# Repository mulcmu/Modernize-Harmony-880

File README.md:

# Modernize Harmony 880
 Modernize a Logitech Harmony 880 universal remote

# Details

The Logitech Harmony 880 is a universal infrared remote intended to control the numerous parts of a home theater system with one remote. The Harmony remotes are programmable allowing sequences of IR commands to be sent to start an activity. So "Watch Blu-ray" could be configured to turn on TV, receiver, and blu-ray player player, and set TV and receiver to correct inputs. Convenient to keep from needing numerous remotes to start an activity. Programming is performed using Logitech internet based software to update the remote via a USB connection. In 2021, Logitech announced that they would discontinue Harmony Remote [manufacturing](https://support.logi.com/hc/en-us/community/posts/1500000658341). The release indicates support would still continue software support, who knows how long that will remain.

The 880 remote build is great quality. I'm not sure exactly when I got mine but it is upwards of 15 years of service with only some cosmetic wear to the buttons. It has a rechargeable battery, that charges in a storage cradle. Over the years the universality of the remote has diminished as more devices use RF remote protocols. To keep the 880 working after getting a Roku box, an ESP8266 needed to be setup to [translate IR remote](https://github.com/mulcmu/IRtoRokuBridge) signals to HTTP POST commands.

This project is undertaking an upgrade for the 880 universal remote to, update screen to TFT with better resolution, build in wifi connectivity, and provide an open source software solution for setup and programming.

Current PCB design has all existing remote features implemented, hardware and software testing in process.

# Project Logs

https://hackaday.io/project/185926-modernize-harmony-880

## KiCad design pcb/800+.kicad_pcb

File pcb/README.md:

# Alpha3 PCB

Alpha3 PCB designed and ordered to test the peripheral operation.  Should be functionally complete if everything works.

There are some clearance issues with the bottom of remote case screw bosses interfering with parts on bottom of board.

# Alpha2 PCB

Updated the Kicad project for another alpha PCB.  Two layer PCB again but 0.8mm thick to fully test fitup with case.

* Fixed mosfet for the button led backlight
* Put an ESP32-S3 module on the board.
* USB wired up to the ESP32, 3.3V supply from the usb 5V.

# Alpha PCB

Kicad files for the alpha PCB.  Overall dimensions were okay.  The sides by the LCD might need trimmed down a smidge but there isn't much room for the button contacts.

Two layer PCB to keep cost down.  I ordered a 1.6mm thick but the stock board was 0.8mm so the case wouldn't snap shut properly.

##### Bare Screen

https://www.alibaba.com/product-detail/Lcd-Screen-Display-2-Inch-240x320_1600053711661.html

##### 4mm dome switches

https://www.aliexpress.us/item/2255799854582341

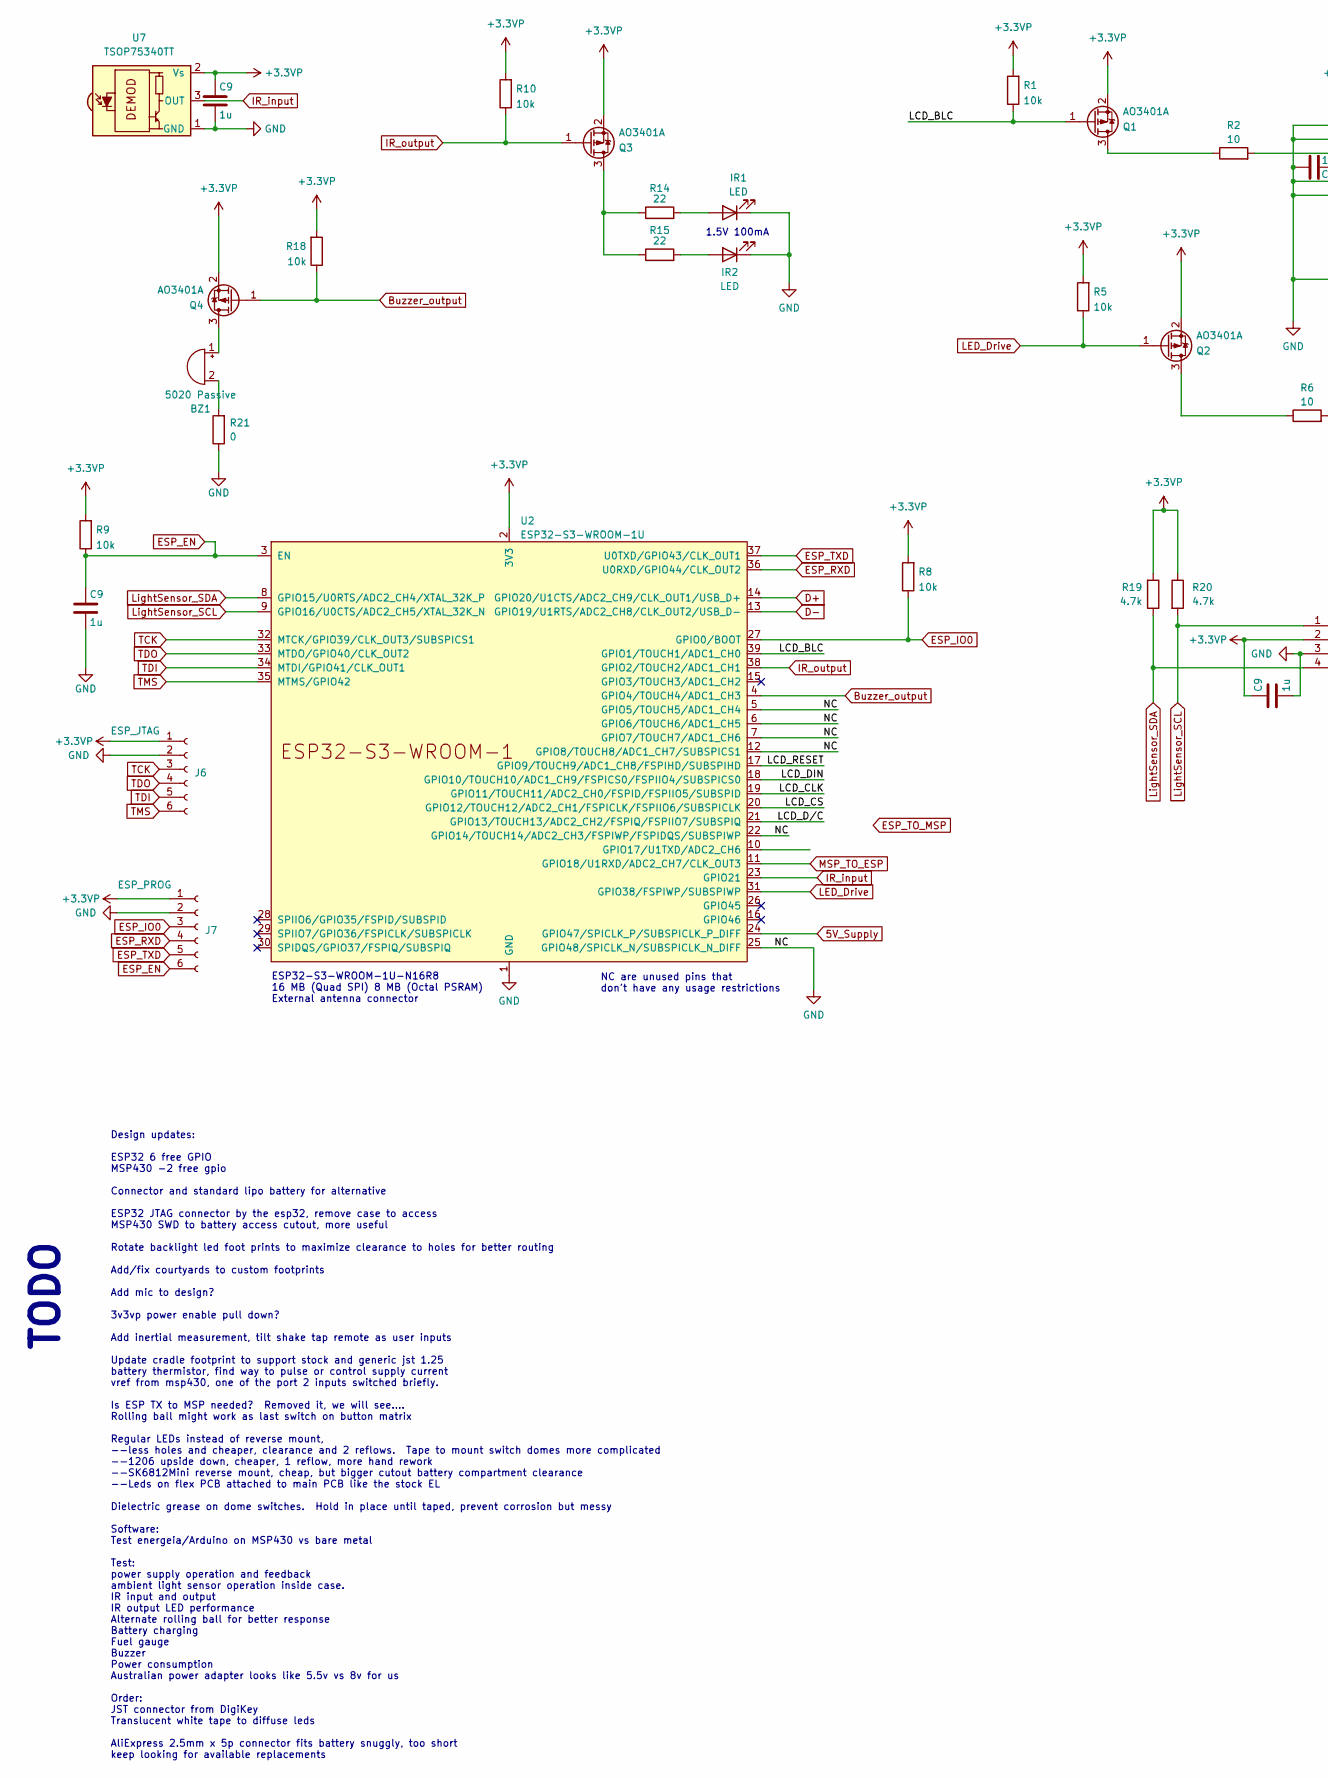
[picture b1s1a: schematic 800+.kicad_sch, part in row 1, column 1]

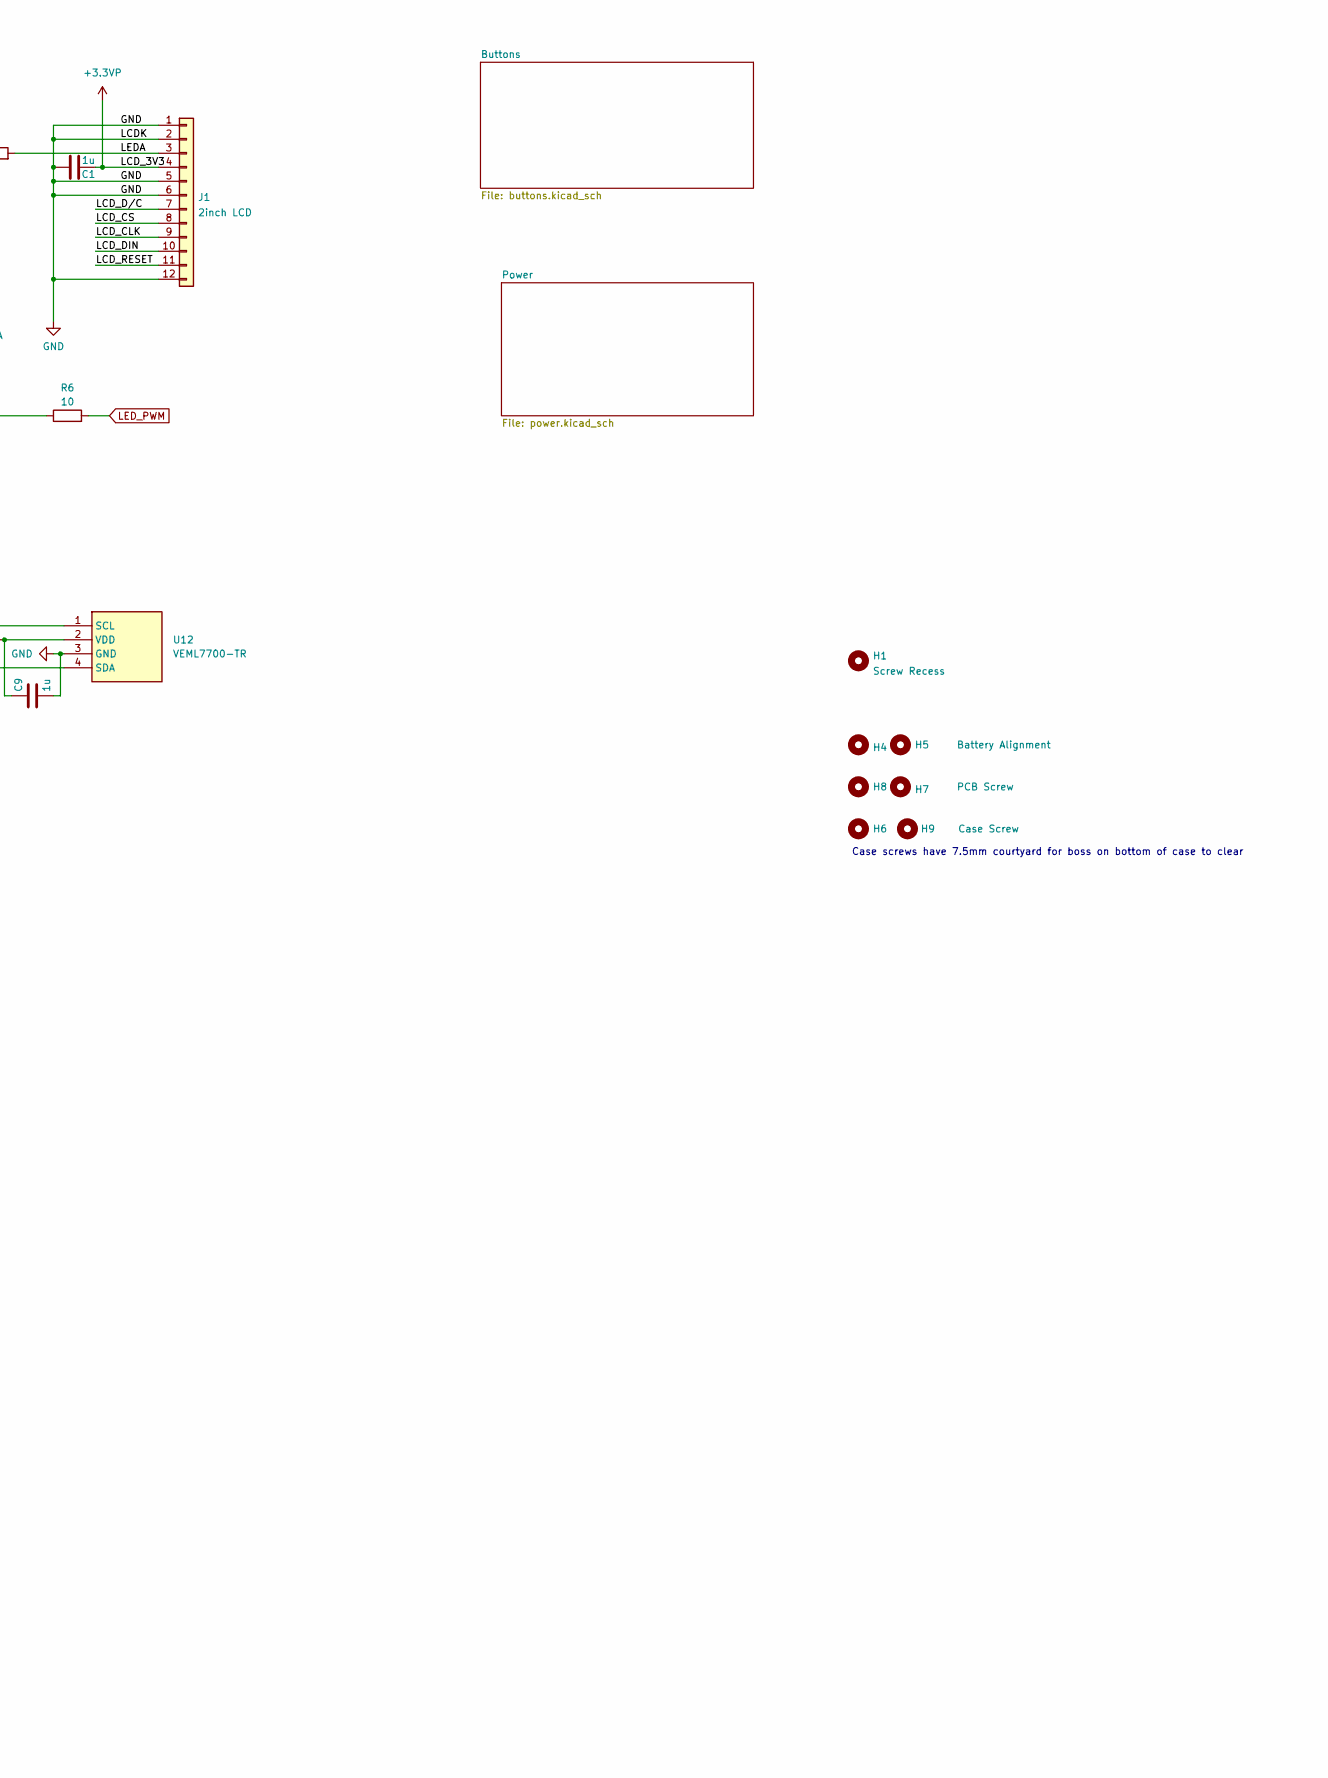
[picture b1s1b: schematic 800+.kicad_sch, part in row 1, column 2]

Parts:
BZ1: 5020 Passive; 5020passiveBuzzer
C1, C9: 1u; C_0805_2012Metric
H1: Screw Recess; MountingHole_5mm
H4, H5: Battery Alignment; MountingHole_2.1mm
H6, H9: Case Screw; MountingHole_Boss
H7, H8: PCB Screw; MountingHole_2.2mm_M2
IR1, IR2: LED; IR_led
J1: 2inch LCD; 2inch_LCD
J6: ESP_JTAG; PinHeader_1x06_P2.54mm_Vertical
J7: ESP_PROG; PinHeader_1x06_P2.54mm_Vertical
Q1, Q2, Q3, Q4: AO3401A; SOT-23
R1, R5, R8, R9, R10, R18: 10k; R_0805_2012Metric
R2, R6: 10; R_1210_3225Metric
R14, R15: 22; R_1210_3225Metric
R19, R20: 4.7k; R_0805_2012Metric
R21: 0; R_1206_3216Metric
U2: ESP32-S3-WROOM-1U; ESP32-S3-WROOM-1
U7: TSOP75340TT; IR_input
U12: VEML7700-TR; VEML7700; Mouser Part Number 78-VEML7700-TT

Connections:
5V_Supply: U2.24 (GPIO47/SPICLK_P/SUBSPICLK_P_DIFF); also elsewhere on the board
/LCD_BLC: Q1.1 (G), R1.1, U2.39 (GPIO1/TOUCH1/ADC1_CH0)
/LCD_CLK: J1.9, U2.19 (GPIO11/TOUCH11/ADC2_CH0/FSPID/FSPIIO5/S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)
/LCD_CS: J1.8, U2.20 (GPIO12/TOUCH12/ADC2_CH1/FSPICLK/FSPIIO6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)
/LCD_DIN: J1.10, U2.18 (GPIO10/TOUCH10/ADC1_CH9/FSPICS0/FSPIIO4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)
/LCD_D/C: J1.7, U2.21 (GPIO13/TOUCH13/ADC2_CH2/FSPIQ/FSPIIO7/S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)
/LCD_RESET: J1.11, U2.17 (GPIO9/TOUCH9/ADC1_CH8/FSPIHD/SUBSPIHD)
/LEDA: J1.3, R2.2
Buzzer_output: Q4.1 (G), R18.1, U2.4 (GPIO4/TOUCH4/ADC1_CH3)
D+: U2.14 (GPIO20/U1CTS/ADC2_CH9/CLK_OUT1/USB_D+); also elsewhere on the board
D-: U2.13 (GPIO19/U1RTS/ADC2_CH8/CLK_OUT2/USB_D-); also elsewhere on the board
ESP_IO0: J7.3, R8.1, U2.27 (GPIO0/BOOT)
ESP_RXD: J7.4, U2.36 (U0RXD/GPIO44/CLK_OUT2)
ESP_TXD: J7.5, U2.37 (U0TXD/GPIO43/CLK_OUT1)
GND: C1.1, C9.2, IR1.1 (K), IR2.1 (K), J1.1, J1.2, J1.5, J1.6, J1.12, J6.2, J7.2, R21.1, U2.1 (GND), U2.5 (GPIO5/TOUCH5/ADC1_CH4), U2.6 (GPIO6/TOUCH6/ADC1_CH5), U2.7 (GPIO7/TOUCH7/ADC1_CH6), U2.12 (GPIO8/TOUCH8/ADC1_CH7/SUBSPICS1), U2.22 (GPIO14/TOUCH14/ADC2_CH3/FSPIWP/FSPIDQS/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), U2.25 (GPIO48/SPICLK_N/SUBSPICLK_N_DIFF), U2.40 (GND), U2.41 (GND), U7.1 (GND), U12.3 (GND); also elsewhere on the board
IR_input: U2.23 (GPIO21), U7.3 (OUT)
IR_output: Q3.1 (G), R10.1, U2.38 (GPIO2/TOUCH2/ADC1_CH1)
LED_Drive: Q2.1 (G), R5.1, U2.31 (GPIO38/FSPIWP/SUBSPIWP)
LED_PWM: R6.2; also elsewhere on the board
LightSensor_SCL: R20.2, U2.9 (GPIO16/U0CTS/ADC2_CH5/XTAL_32K_N), U12.1 (SCL)
LightSensor_SDA: R19.1, U2.8 (GPIO15/U0RTS/ADC2_CH4/XTAL_32K_P), U12.4 (SDA)
MSP_TO_ESP: U2.11 (GPIO18/U1RXD/ADC2_CH7/CLK_OUT3); also elsewhere on the board
unnamed: BZ1.1 (+), Q4.3 (D)
unnamed: BZ1.2 (-), R21.2
unnamed: IR1.2 (A), R14.2
unnamed: IR2.2 (A), R15.2
unnamed: Q1.3 (D), R2.1
unnamed: Q2.3 (D), R6.1
unnamed: Q3.3 (D), R14.1, R15.1
TCK: J6.3, U2.32 (MTCK/GPIO39/CLK_OUT3/SUBSPICS1)
TDI: J6.5, U2.34 (MTDI/GPIO41/CLK_OUT1)
TDO: J6.4, U2.33 (MTDO/GPIO40/CLK_OUT2)
TMS: J6.6, U2.35 (MTMS/GPIO42)

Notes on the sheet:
NC are unused pins that don't have any usage restrictions
TODO
Case screws have 7.5mm courtyard for boss on bottom of case to clear
1.5V 100mA
Design updates: ESP32 6 free GPIO MSP430 -2 free gpio Connector and standard lipo battery for alternative ESP32 JTAG connector by the esp32, remove case to access MSP430 SWD to battery access cutout, more useful Rotate backlight led foot prints to maximize clearance to holes for better routing Add/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
ESP32-S3-WROOM-1U-N16R8 16 MB (Quad SPI) 8 MB (Octal PSRAM) External antenna connector

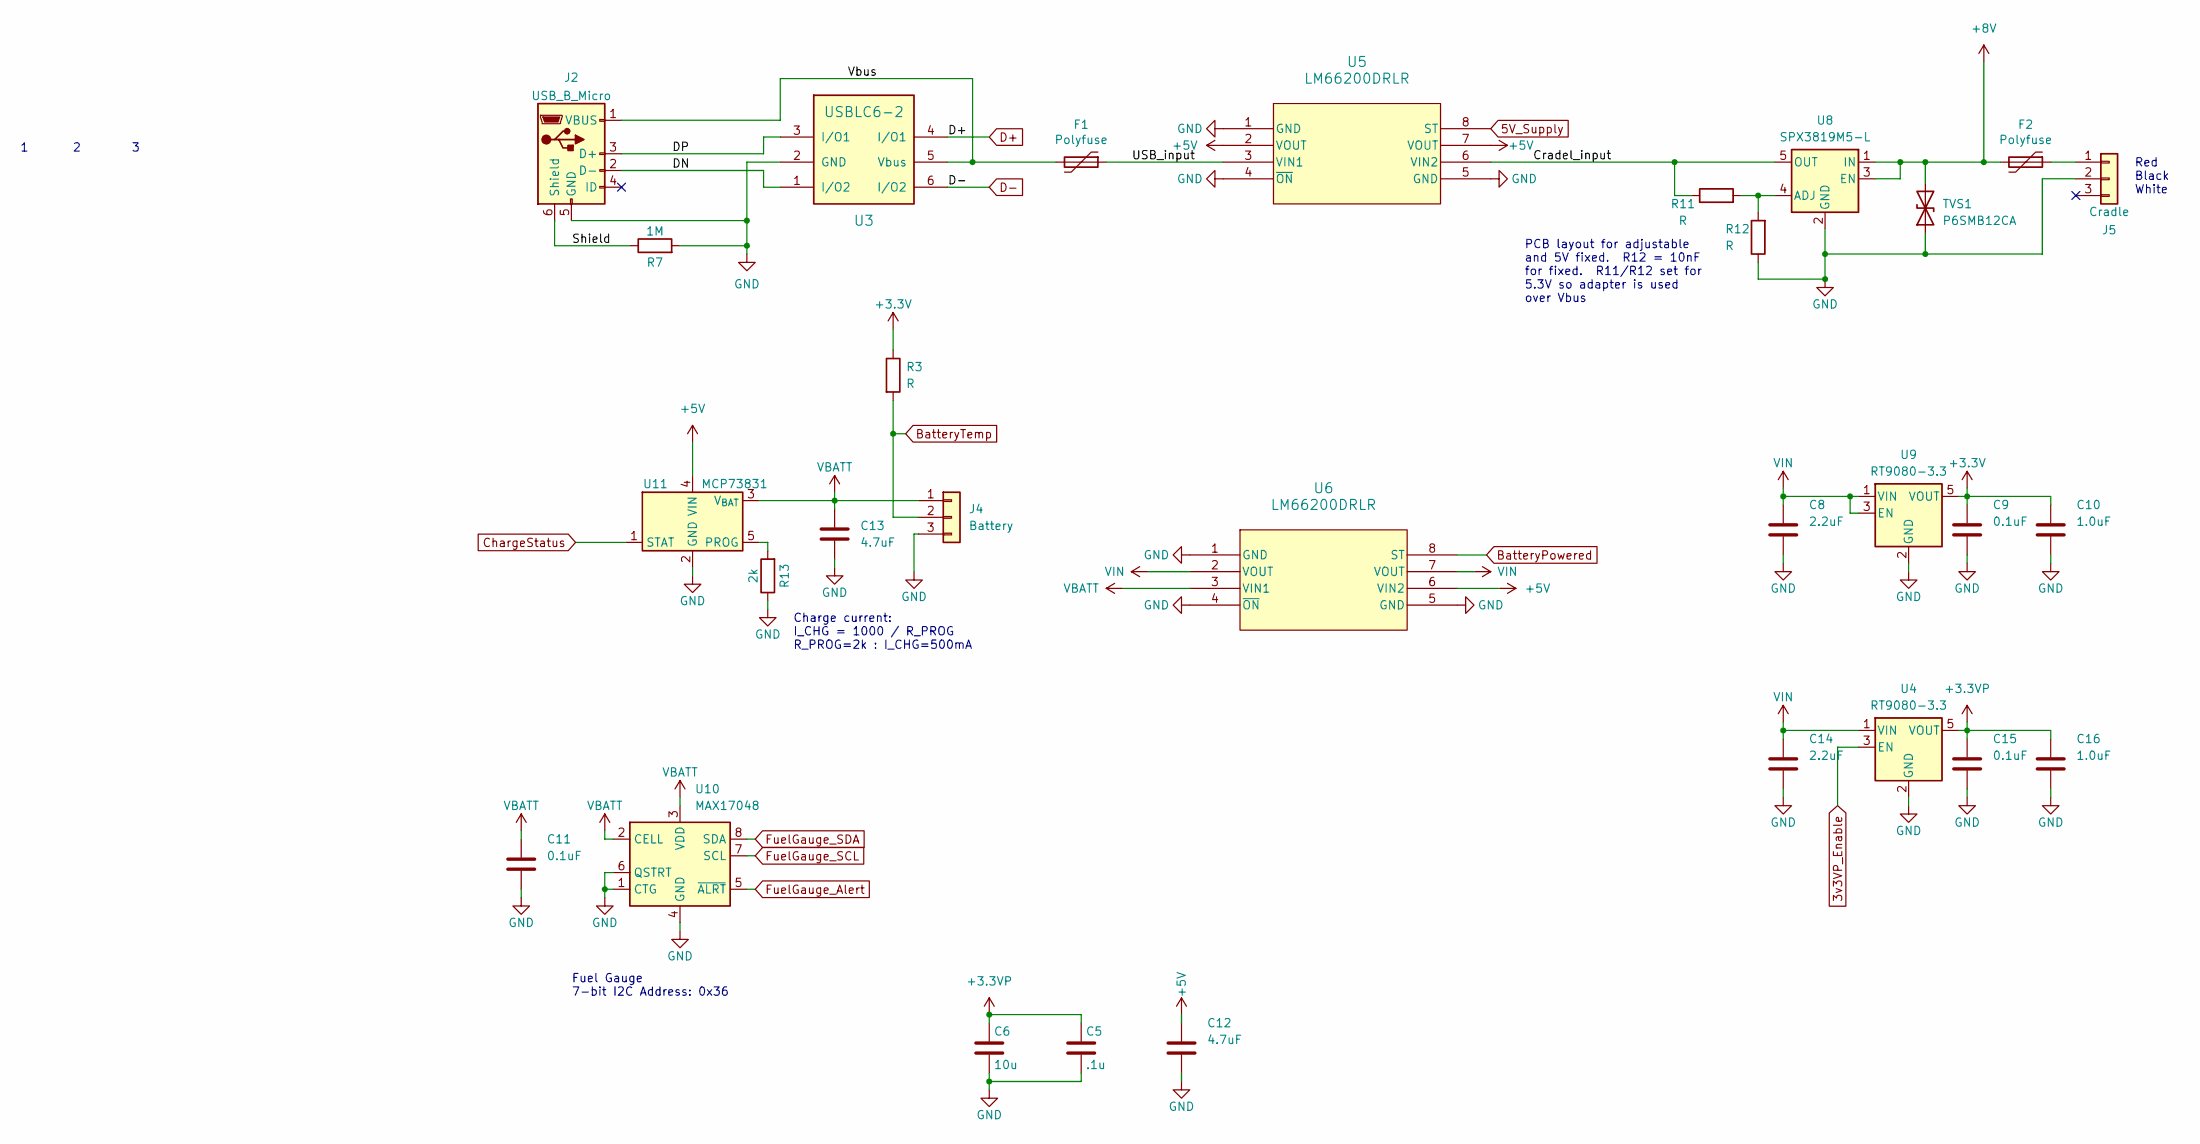
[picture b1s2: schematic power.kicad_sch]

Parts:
C5: .1u; C_0805_2012Metric
C6: 10u; C_0805_2012Metric
C8, C14: 2.2uF; C_0805_2012Metric
C9, C11, C15: 0.1uF; C_0805_2012Metric
C10, C16: 1.0uF; C_0805_2012Metric
C12, C13: 4.7uF; C_0805_2012Metric
F1, F2: Polyfuse; R_1210_3225Metric_Pad1.30x2.65mm_HandSolder
J2: USB_B_Micro; USB_Mini-B_Wuerth_65100516121_Horizontal
J4: Battery; Battery_reuse
J5: Cradle; JST_GH_BM03B-GHS-TBT_1x03-1MP_P1.25mm_Vertical
R3, R11, R12: R; R_0805_2012Metric
R7: 1M; R_0805_2012Metric
R13: 2k; R_0805_2012Metric
TVS1: P6SMB12CA; D_SMB
U3: USBLC6-2; SOT-23-6
U4, U9: RT9080-3.3; SOT-23-5
U5, U6: LM66200DRLR; SOT-583-8
U8: SPX3819M5-L; SOT-23-5
U10: MAX17048; TDFN-8-1EP_2x2mm_P0.5mm_EP0.8x1.4mm
U11: MCP73831; SOT-23-5

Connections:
3v3VP_Enable: U4.3 (EN); also elsewhere on the board
5V_Supply: U5.8 (ST); also elsewhere on the board
+5V: C12.1, U5.2 (VOUT), U5.7 (VOUT), U6.6 (VIN2), U11.4 (VIN)
+8V: F2.2, TVS1.2 (A2), U8.1 (IN), U8.3 (EN)
/Power/Cradel_input: R11.1, U5.6 (VIN2), U8.5 (OUT)
/Power/DN: J2.2 (D-), U3.1 (I/O2)
/Power/DP: J2.3 (D+), U3.3 (I/O1)
/Power/Shield: J2.6 (Shield), R7.1
/Power/USB_input: F1.1, U5.3 (VIN1)
/Power/Vbus: F1.2, J2.1 (VBUS), U3.5 (Vbus)
BatteryPowered: U6.8 (ST); also elsewhere on the board
BatteryTemp: J4.2, R3.2; also elsewhere on the board
ChargeStatus: U11.1 (STAT); also elsewhere on the board
D+: U3.4 (I/O1); also elsewhere on the board
D-: U3.6 (I/O2); also elsewhere on the board
FuelGauge_Alert: U10.5 (~ALRT); also elsewhere on the board
FuelGauge_SCL: U10.7 (SCL); also elsewhere on the board
FuelGauge_SDA: U10.8 (SDA); also elsewhere on the board
GND: C5.2, C6.2, C8.2, C9.2, C10.2, C11.2, C12.2, C13.2, C14.2, C15.2, C16.2, J2.5 (GND), J4.3, J5.2, R7.2, R12.1, R13.1, TVS1.1 (A1), U3.2 (GND), U4.2 (GND), U5.1 (GND), U5.4 (~ON), U5.5 (GND), U6.1 (GND), U6.4 (~ON), U6.5 (GND), U8.2 (GND), U9.2 (GND), U10.1 (CTG), U10.4 (GND), U10.6 (QSTRT), U10.9 (GND), U11.2 (GND); also elsewhere on the board
unnamed: F2.1, J5.1
unnamed: R11.2, R12.2, U8.4 (ADJ)
unnamed: R13.2, U11.5 (PROG)
VBATT: C11.1, C13.1, J4.1, U6.3 (VIN1), U10.2 (CELL), U10.3 (VDD), U11.3 (V_{BAT})
VIN: C8.1, C14.1, U4.1 (VIN), U6.2 (VOUT), U6.7 (VOUT), U9.1 (VIN), U9.3 (EN)

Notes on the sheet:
Fuel Gauge 7-bit I2C Address: 0x36
PCB layout for adjustable and 5V fixed. R12 = 10nF for fixed. R11/R12 set for 5.3V so adapter is used over Vbus
Red Black White
Charge current: I_CHG = 1000 / R_PROG R_PROG=2k : I_CHG=500mA
1 2 3

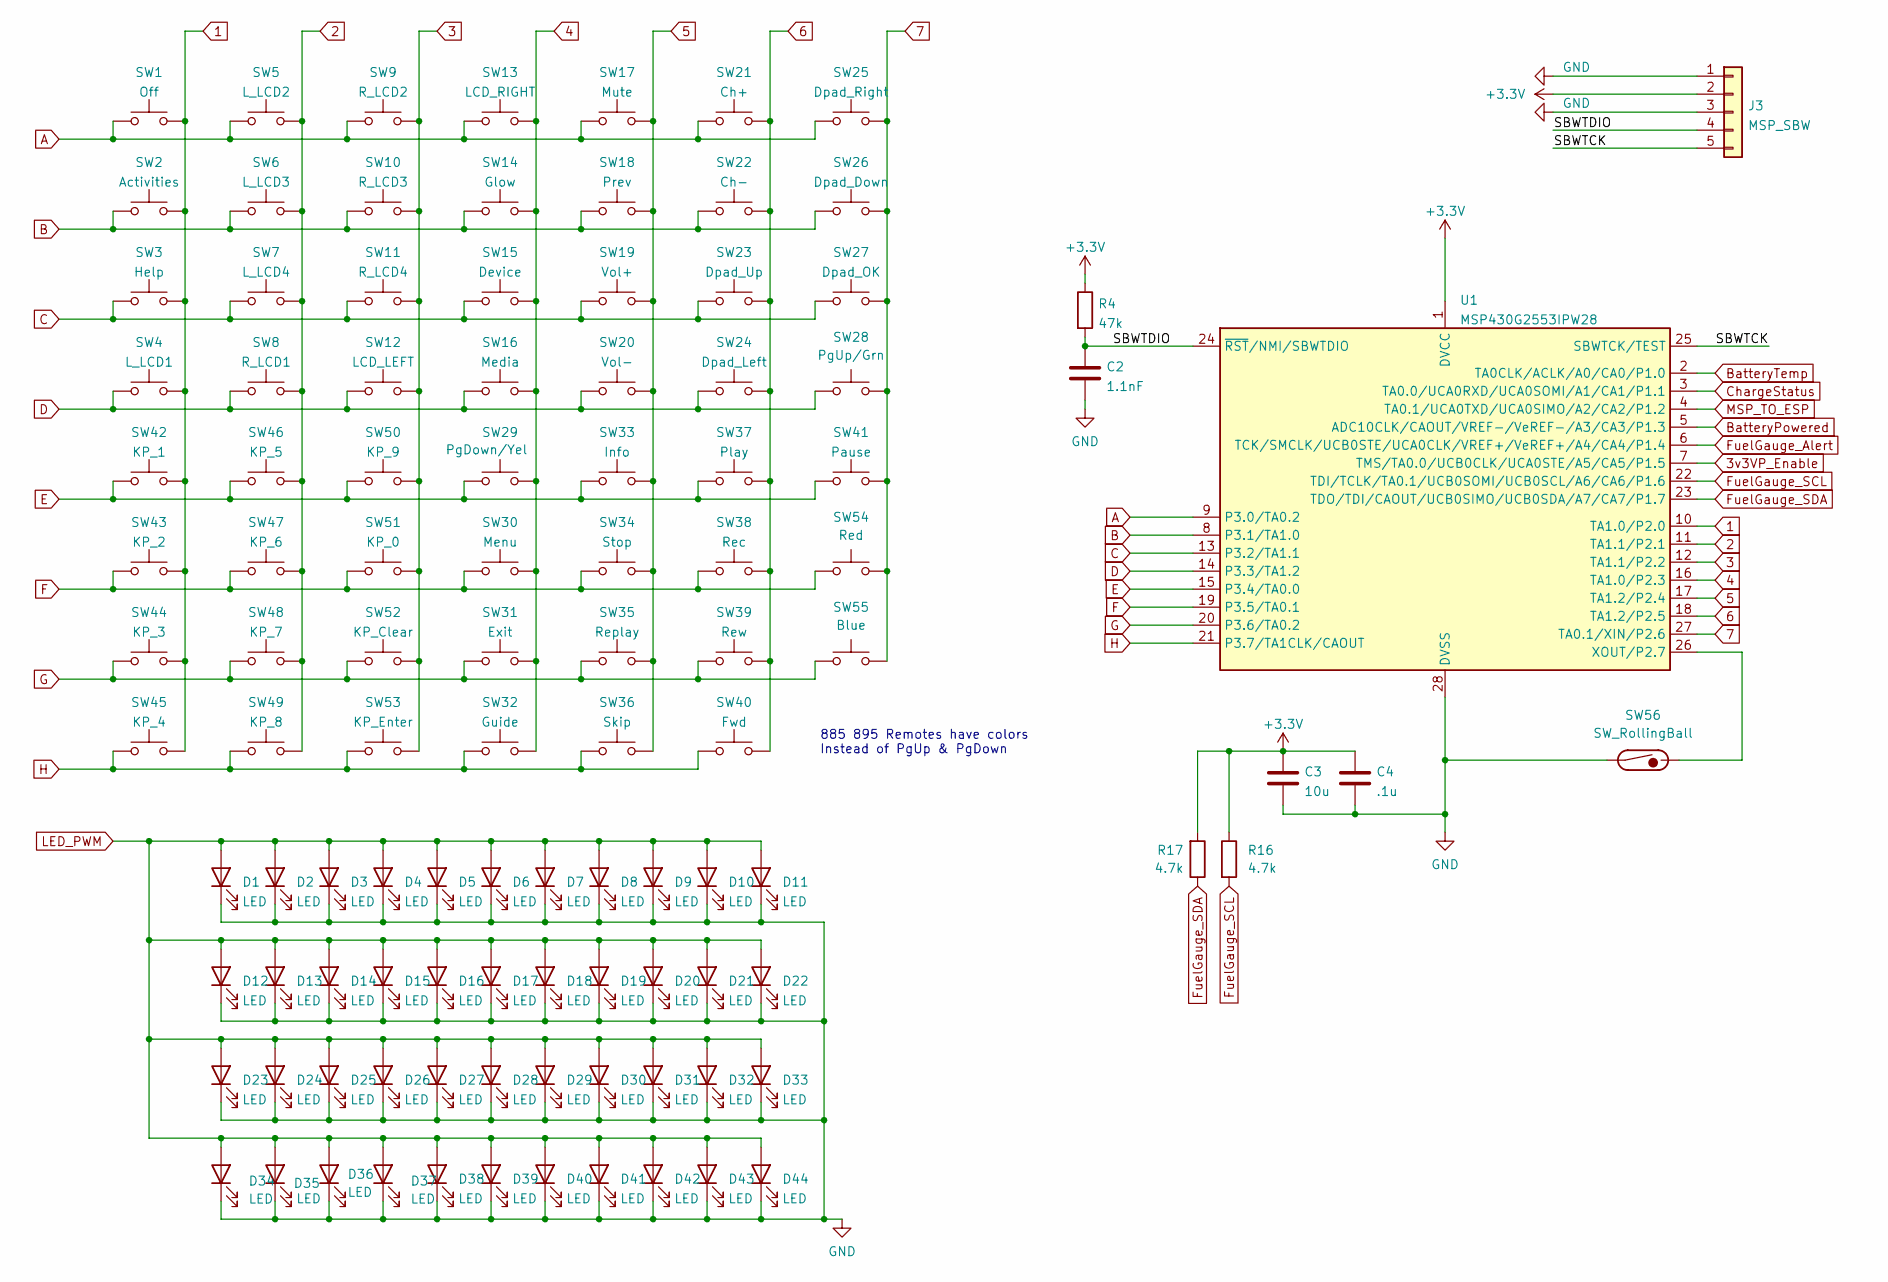
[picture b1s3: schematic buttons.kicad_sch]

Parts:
C2: 1.1nF; C_0805_2012Metric
C3: 10u; C_0805_2012Metric
C4: .1u; C_0805_2012Metric
D1, D2, D3, D4, D5, D6, D7, D8, D9, D10, D11, D12, D13, D14, D15, D16, D17, D18, D19, D20, D21, D22, D23, D24, D25, D26, D27, D28, D29, D30, D31, D32, D33, D34, D35, D36, D37, D38, D39, D40, D41, D42, D43, D44: LED; C265_reverse_mount_led_DRC
J3: MSP_SBW; PinHeader_1x05_P2.54mm_Vertical
R4: 47k; R_0805_2012Metric
R16, R17: 4.7k; R_0805_2012Metric
SW1: Off; 4mm Dome
SW2: Activities; 4mm Dome
SW3: Help; 4mm Dome
SW4: L_LCD1; 4mm Dome
SW5: L_LCD2; 4mm Dome
SW6: L_LCD3; 4mm Dome
SW7: L_LCD4; 4mm Dome
SW8: R_LCD1; 4mm Dome
SW9: R_LCD2; 4mm Dome
SW10: R_LCD3; 4mm Dome
SW11: R_LCD4; 4mm Dome
SW12: LCD_LEFT; 4mm Dome
SW13: LCD_RIGHT; 4mm Dome
SW14: Glow; 4mm Dome
SW15: Device; 4mm Dome
SW16: Media; 4mm Dome
SW17: Mute; 4mm Dome
SW18: Prev; 4mm Dome
SW19: Vol+; 4mm Dome
SW20: Vol-; 4mm Dome
SW21: Ch+; 4mm Dome
SW22: Ch-; 4mm Dome
SW23: Dpad_Up; 4mm Dome
SW24: Dpad_Left; 4mm Dome
SW25: Dpad_Right; 4mm Dome
SW26: Dpad_Down; 4mm Dome
SW27: Dpad_OK; 4mm Dome
SW28: PgUp/Grn; 4mm Dome
SW29: PgDown/Yel; 4mm Dome
SW30: Menu; 4mm Dome
SW31: Exit; 4mm Dome
SW32: Guide; 4mm Dome
SW33: Info; 4mm Dome
SW34: Stop; 4mm Dome
SW35: Replay; 4mm Dome
SW36: Skip; 4mm Dome
SW37: Play; 4mm Dome
SW38: Rec; 4mm Dome
SW39: Rew; 4mm Dome
SW40: Fwd; 4mm Dome
SW41: Pause; 4mm Dome
SW42: KP_1; 4mm Dome
SW43: KP_2; 4mm Dome
SW44: KP_3; 4mm Dome
SW45: KP_4; 4mm Dome
SW46: KP_5; 4mm Dome
SW47: KP_6; 4mm Dome
SW48: KP_7; 4mm Dome
SW49: KP_8; 4mm Dome
SW50: KP_9; 4mm Dome
SW51: KP_0; 4mm Dome
SW52: KP_Clear; 4mm Dome
SW53: KP_Enter; 4mm Dome
SW54: Red; 4mm Dome
SW55: Blue; 4mm Dome
SW56: SW_RollingBall; R_1210_3225Metric
U1: MSP430G2553IPW28; TSSOP-28_4.4x9.7mm_P0.65mm

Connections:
1: SW1.2, SW2.2, SW3.2, SW4.2, SW42.2, SW43.2, SW44.2, SW45.2, U1.10 (TA1.0/P2.0)
2: SW5.2, SW6.2, SW7.2, SW8.2, SW46.2, SW47.2, SW48.2, SW49.2, U1.11 (TA1.1/P2.1)
3: SW9.2, SW10.2, SW11.2, SW12.2, SW50.2, SW51.2, SW52.2, SW53.2, U1.12 (TA1.1/P2.2)
3v3VP_Enable: U1.7 (TMS/TA0.0/UCB0CLK/UCA0STE/A5/CA5/P1.5); also elsewhere on the board
4: SW13.2, SW14.2, SW15.2, SW16.2, SW29.2, SW30.2, SW31.2, SW32.2, U1.16 (TA1.0/P2.3)
5: SW17.2, SW18.2, SW19.2, SW20.2, SW33.2, SW34.2, SW35.2, SW36.2, U1.17 (TA1.2/P2.4)
6: SW21.2, SW22.2, SW23.2, SW24.2, SW37.2, SW38.2, SW39.2, SW40.2, U1.18 (TA1.2/P2.5)
7: SW25.2, SW26.2, SW27.2, SW28.2, SW41.2, SW54.2, SW55.2, U1.27 (TA0.1/XIN/P2.6)
/Buttons/SBWTCK: J3.5, U1.25 (SBWTCK/TEST)
/Buttons/SBWTDIO: C2.1, J3.4, R4.2, U1.24 (~RST/NMI/SBWTDIO)
A: SW1.1, SW5.1, SW9.1, SW13.1, SW17.1, SW21.1, SW25.1, U1.9 (P3.0/TA0.2)
B: SW2.1, SW6.1, SW10.1, SW14.1, SW18.1, SW22.1, SW26.1, U1.8 (P3.1/TA1.0)
BatteryPowered: U1.5 (ADC10CLK/CAOUT/VREF-/VeREF-/A3/CA3/P1.3); also elsewhere on the board
BatteryTemp: U1.2 (TA0CLK/ACLK/A0/CA0/P1.0); also elsewhere on the board
C: SW3.1, SW7.1, SW11.1, SW15.1, SW19.1, SW23.1, SW27.1, U1.13 (P3.2/TA1.1)
ChargeStatus: U1.3 (TA0.0/UCA0RXD/UCA0SOMI/A1/CA1/P1.1); also elsewhere on the board
D: SW4.1, SW8.1, SW12.1, SW16.1, SW20.1, SW24.1, SW28.1, U1.14 (P3.3/TA1.2)
E: SW29.1, SW33.1, SW37.1, SW41.1, SW42.1, SW46.1, SW50.1, U1.15 (P3.4/TA0.0)
F: SW30.1, SW34.1, SW38.1, SW43.1, SW47.1, SW51.1, SW54.1, U1.19 (P3.5/TA0.1)
FuelGauge_Alert: U1.6 (TCK/SMCLK/UCB0STE/UCA0CLK/VREF+/VeREF+/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); also elsewhere on the board
FuelGauge_SCL: R16.2, U1.22 (TDI/TCLK/TA0.1/UCB0SOMI/UCB0SCL/A6/CA6/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); also elsewhere on the board
FuelGauge_SDA: R17.1, U1.23 (TDO/TDI/CAOUT/UCB0SIMO/UCB0SDA/A7/CA7/P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); also elsewhere on the board
G: SW31.1, SW35.1, SW39.1, SW44.1, SW48.1, SW52.1, SW55.1, U1.20 (P3.6/TA0.2)
GND: C2.2, C3.2, C4.2, D1.1 (K), D2.1 (K), D3.1 (K), D4.1 (K), D5.1 (K), D6.1 (K), D7.1 (K), D8.1 (K), D9.1 (K), D10.1 (K), D11.1 (K), D12.1 (K), D13.1 (K), D14.1 (K), D15.1 (K), D16.1 (K), D17.1 (K), D18.1 (K), D19.1 (K), D20.1 (K), D21.1 (K), D22.1 (K), D23.1 (K), D24.1 (K), D25.1 (K), D26.1 (K), D27.1 (K), D28.1 (K), D29.1 (K), D30.1 (K), D31.1 (K), D32.1 (K), D33.1 (K), D34.1 (K), D35.1 (K), D36.1 (K), D37.1 (K), D38.1 (K), D39.1 (K), D40.1 (K), D41.1 (K), D42.1 (K), D43.1 (K), D44.1 (K), J3.1, J3.3, SW56.1, U1.28 (DVSS); also elsewhere on the board
H: SW32.1, SW36.1, SW40.1, SW45.1, SW49.1, SW53.1, U1.21 (P3.7/TA1CLK/CAOUT)
LED_PWM: D1.2 (A), D2.2 (A), D3.2 (A), D4.2 (A), D5.2 (A), D6.2 (A), D7.2 (A), D8.2 (A), D9.2 (A), D10.2 (A), D11.2 (A), D12.2 (A), D13.2 (A), D14.2 (A), D15.2 (A), D16.2 (A), D17.2 (A), D18.2 (A), D19.2 (A), D20.2 (A), D21.2 (A), D22.2 (A), D23.2 (A), D24.2 (A), D25.2 (A), D26.2 (A), D27.2 (A), D28.2 (A), D29.2 (A), D30.2 (A), D31.2 (A), D32.2 (A), D33.2 (A), D34.2 (A), D35.2 (A), D36.2 (A), D37.2 (A), D38.2 (A), D39.2 (A), D40.2 (A), D41.2 (A), D42.2 (A), D43.2 (A), D44.2 (A); also elsewhere on the board
MSP_TO_ESP: U1.4 (TA0.1/UCA0TXD/UCA0SIMO/A2/CA2/P1.2); also elsewhere on the board
unnamed: SW56.2, U1.26 (XOUT/P2.7)

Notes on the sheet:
885 895 Remotes have colors Instead of PgUp & PgDown

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
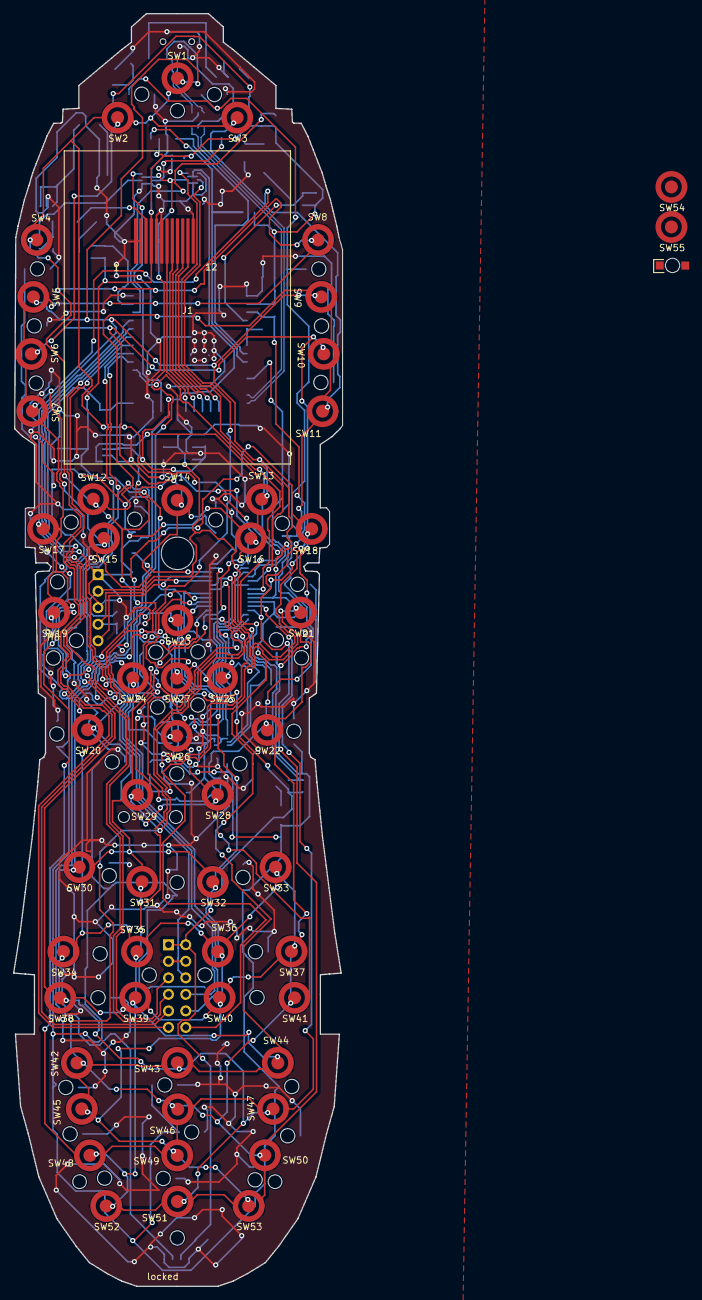
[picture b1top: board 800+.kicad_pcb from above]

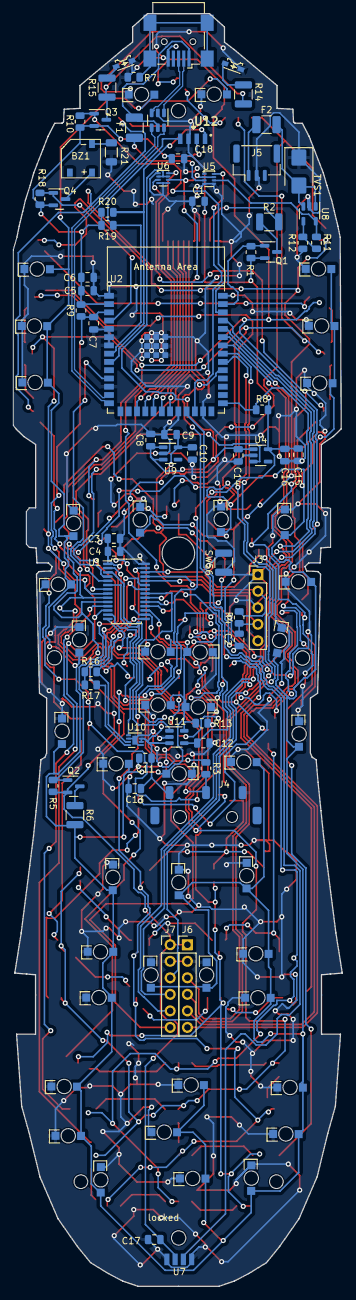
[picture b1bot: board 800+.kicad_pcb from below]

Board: 2 copper layers, 50.5 x 195.6 mm, 175 parts (111 on the bottom side), 74 nets.

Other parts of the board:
C7, C17, C18: 1u; C_0805_2012Metric

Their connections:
GND: C7.2, C17.2, C18.2; also elsewhere on the board

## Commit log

2023-03-14 alpha pcb
2023-03-14 msp430 test code
2024-05-07 alpha2 pcb
2024-05-23 add blink demo for alpha2 esp32
2024-05-23 buttons working from msp to esp
2024-05-23 msp430 from ccs to platformio
2024-05-29 msp430 structure
    button logic changed to look up tables. 200 bytes less flash than the switch statements and faster
2024-05-31 esp & msp code
    add shock sensor to P2.7
2024-06-01 current working kikad
2024-06-04 lvgl test
2024-06-04 EEZ ui, LVGL 9.1x working
2024-06-04 cleanup
2024-06-04 lvgl9 working
2024-06-06 add power to schematic
2024-06-07 more schematic updates
2024-06-07 ready to route????
2024-06-10 fix battery connector
2024-06-11 cradle connector
2024-06-13 parts placed
2024-06-14 alpha3 pcb
2024-06-14 fix VEML7700 direction
2024-06-14 footprints
2024-06-20 readme updates
2024-06-22 somewhat working
2024-06-22 even with main except lpm
2024-06-23 prep for alpha3 pcb
2024-06-23 update todo and reference info
2024-06-24 update case screws
    bottom courtyard added for case screws to account for boss on the case
2024-06-26 msp edits
2024-06-27 baseline alpha3 code
2024-06-28 mounting boss
2024-06-29 fix for serial.begin() blocking and tft.init() panic
    esp 3.0.2
    and tft_espi 2.5.43
2024-06-29 todo
2024-06-29 ESP32 IR Recv
    Back to esp 2.0.17 for IRremote lib
2024-06-29 IR led fix
2024-06-30 lux and buzzer
2024-06-30 more esp code
2024-08-29 library updates
    LVGL 9.2 is released
    Everything working with ESP board 3.0.3
    tft configuration in sketch folder
